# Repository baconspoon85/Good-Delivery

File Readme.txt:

Good Delivery is a pair of 10x4u PCBs featuring:
-Standard stagger layout
	Proto built and tested. Fully functional.
-Alpha stagger layout
	Proto pending.
-RP2040 MCU
-Hotswap MX support (w/ option to solder the corner switches for better o-ring stability with 3-pin switches)
-Solder Alps support
-Physical compatibility with Acai by CBKBD
	-Centered USB
	-Gummy O-ring mount

Vial firmware supporting both the standard row stagger and alpha stagger is complete, courtesy of Flamwenco! Big thank you. Check his Cutiepie repo, also forked on my page.

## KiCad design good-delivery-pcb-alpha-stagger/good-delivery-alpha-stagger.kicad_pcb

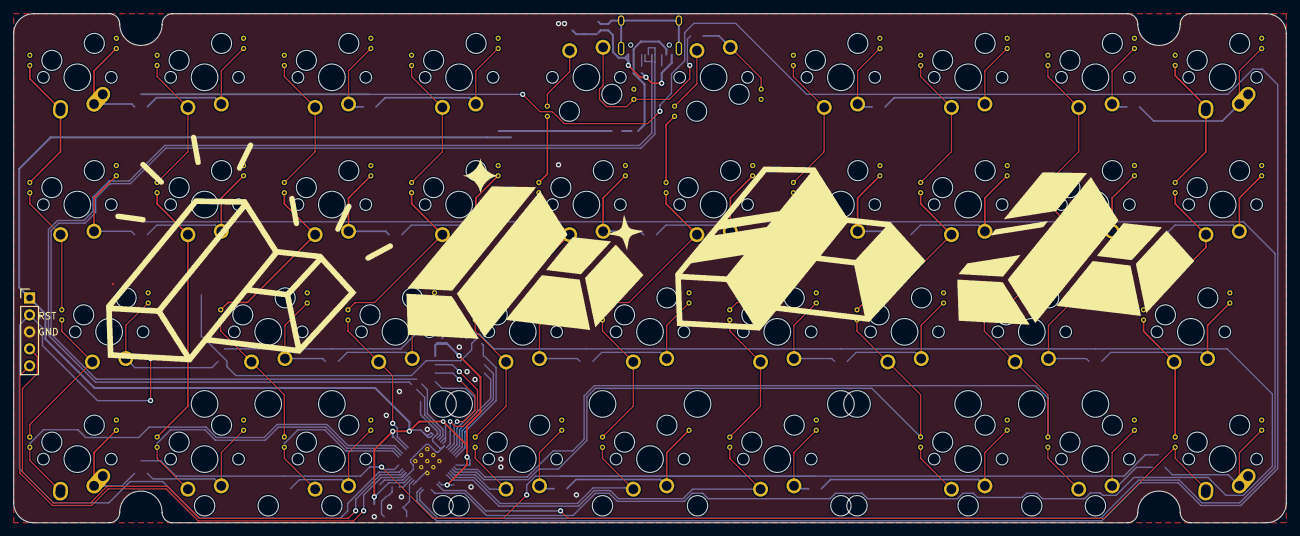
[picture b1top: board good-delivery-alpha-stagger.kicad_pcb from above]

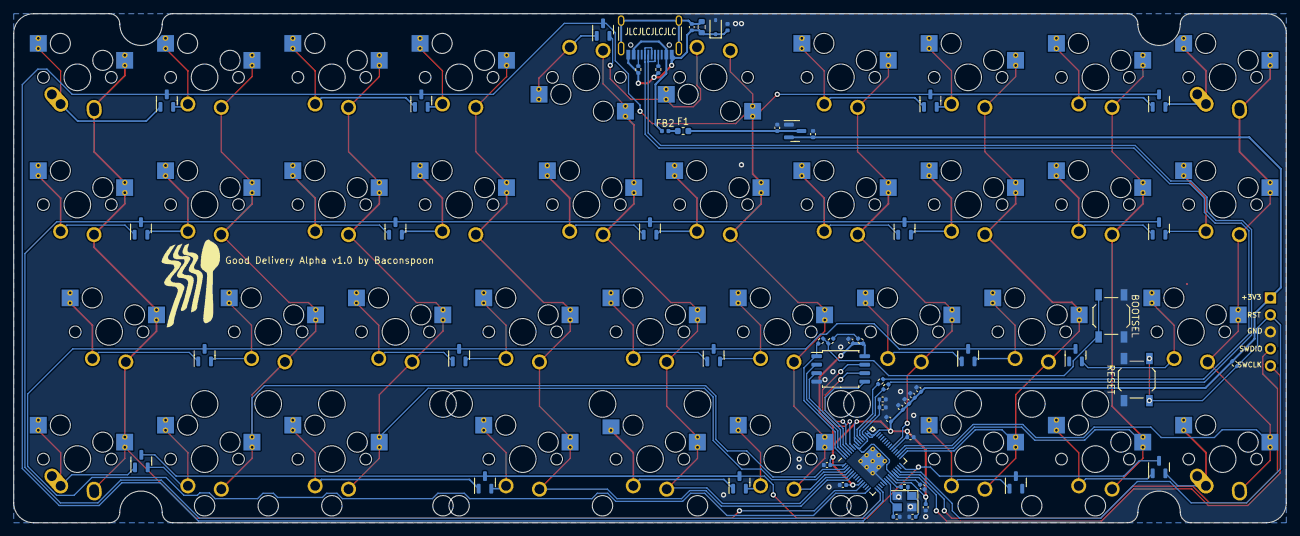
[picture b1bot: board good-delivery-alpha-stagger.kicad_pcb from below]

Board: 2 copper layers, 190.5 x 76.2 mm, 100 parts (60 on the bottom side), 80 nets.

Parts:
C1: 100nF; C_0402_1005Metric
C_1V-Decoup1, C_3V-Decoup2: 1u; C_0402_1005Metric
C_1V-Decoup2, C_1V-Decoup3, C_3V-Decoup3, C_3V-Decoup4, C_3V-Decoup5, C_3V-Decoup6, C_3V-Decoup7, C_3V-Decoup8, C_3V-Decoup9: 100n; C_0402_1005Metric
C_3V-Decoup1: 10u; C_0402_1005Metric
C_Crystal1, C_Crystal2: 22p; C_0402_1005Metric
C_Flash1: 100n; C_0402_1005Metric
C_LD1, C_LD2: 1u; C_0402_1005Metric
D1, D2, D3, D4, D5, D6, D7, D8, D9, D10, D11, D12, D13, D14, D15, D16, D17, D18, D19, D20: BAV70; SOT-23
D21: BSD3C051V; D_SOD-323
F1: 0603L075SLYR; Fuse_0603_1608Metric
FB1, FB2: BLM15PX121SN1D; L_0402_1005Metric
G1: Logo_Open_Hardware_Small; good-delivery-bars-silkscreen
G2: Logo_Open_Hardware_Small; baconspoon-logo-15mm
J2: SWD; PinHeader_1x05_P2.54mm_Vertical
J3: USB_C_Receptacle_USB2.0; USB_C_Receptacle_HRO_TYPE-C-31-M-12
MX1, MX4, MX5, MX6, MX7, MX8, MX9, MX10, MX11, MX12, MX13, MX14, MX15, MX16, MX17, MX18, MX20, MX21, MX22, MX24, MX25, MX26, MX28, MX29, MX30, MX31, MX32, MX33, MX34, MX35, MX38: MX-NoLED; 1U-MX-Hotswap-Alps-Solder-PadSwapped
MX2, MX36: MX-NoLED; 1U-MX-Hotswap-Alps-Solder
MX3, MX37: MX-NoLED; 1.5U-MX-Hotswap-Alps-Solder
MX19, MX27: MX-NoLED; 2U-MX-Hotswap-Alps-Solder-PadSwapped-ReversedStabilizers
MX23: MX-NoLED; 4,6,7,8,10u-MX-Hotswap-Alps-Solder-PadSwapped-ReversedStabi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
R1: 1M; R_0603_1608Metric
R2, R3: 5k1; R_0402_1005Metric
R_Crystal1: 1k; R_0402_1005Metric
R_DATA1, R_DATA2: 27; R_0402_1005Metric
R_Flash1, R_Flash2: 5k1; R_0402_1005Metric
R_Flash3: 1k; R_0402_1005Metric
R_RST1: 5k1; R_0402_1005Metric
SW1: RESET; SW_SPST_TL3342
SW2: BOOTSEL; SW_SPST_TL3342
U1: RP2040; RP2040-QFN-56
U2: W25Q128JVS; SOIC-8_5.23x5.23mm_P1.27mm
U3: XC6206P332MR; SOT-23
Y1: 12MHz; Crystal_SMD_3225-4Pin_3.2x2.5mm

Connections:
+1V1: C_1V-Decoup1.1, C_1V-Decoup2.1, C_1V-Decoup3.1, U1.23 (DVDD), U1.45 (VREG_VOUT), U1.50 (DVDD)
+3V3: C_3V-Decoup1.1, C_3V-Decoup2.1, C_3V-Decoup3.1, C_3V-Decoup4.1, C_3V-Decoup5.1, C_3V-Decoup6.1, C_3V-Decoup7.1, C_3V-Decoup8.1, C_3V-Decoup9.1, C_Flash1.1, C_LD2.1, J2.1, R_Flash1.1, R_RST1.1, U1.1 (IOVDD), U1.10 (IOVDD), U1.22 (IOVDD), U1.33 (IOVDD), U1.42 (IOVDD), U1.43 (ADC_AVDD), U1.44 (VREG_IN), U1.48 (USB_VDD), U1.49 (IOVDD), U2.8 (VCC), U3.2 (VO)
+5V: C_LD1.1, F1.2, U3.3 (VI)
COL 0: MX1.1 (COL), MX2.1 (COL), MX3.1 (COL), MX4.1 (COL), U1.31 (GPIO20)
COL 1: MX6.1 (COL), MX7.1 (COL), MX8.1 (COL), U1.30 (GPIO19)
COL 2: MX9.1 (COL), MX10.1 (COL), MX11.1 (COL), MX12.1 (COL), U1.29 (GPIO18)
COL 3: MX13.1 (COL), MX14.1 (COL), MX15.1 (COL), U1.34 (GPIO22)
COL 4: MX16.1 (COL), MX17.1 (COL), MX18.1 (COL), MX19.1 (COL), U1.4 (GPIO2)
COL 5: MX20.1 (COL), MX21.1 (COL), MX22.1 (COL), MX23.1 (COL), U1.5 (GPIO3)
COL 6: MX24.1 (COL), MX25.1 (COL), MX26.1 (COL), MX27.1 (COL), U1.6 (GPIO4)
COL 7: MX28.1 (COL), MX29.1 (COL), MX30.1 (COL), MX31.1 (COL), U1.3 (GPIO1)
COL 8: MX5.1 (COL), MX32.1 (COL), MX33.1 (COL), MX34.1 (COL), U1.2 (GPIO0)
COL 9: MX35.1 (COL), MX36.1 (COL), MX37.1 (COL), MX38.1 (COL), U1.11 (GPIO8)
CS: R_Flash3.2, U1.56 (QSPI_SS), U2.1 (~CS)
D+: J3.A6 (D+), J3.B6 (D+), R_DATA1.1
D-: J3.A7 (D-), J3.B7 (D-), R_DATA2.1
Earth: C1.1, J3.S1 (SHIELD), R1.1
GND: C_1V-Decoup1.2, C_1V-Decoup2.2, C_1V-Decoup3.2, C_3V-Decoup1.2, C_3V-Decoup2.2, C_3V-Decoup3.2, C_3V-Decoup4.2, C_3V-Decoup5.2, C_3V-Decoup6.2, C_3V-Decoup7.2, C_3V-Decoup8.2, C_3V-Decoup9.2, C_Crystal1.1, C_Crystal2.1, C_Flash1.2, C_LD1.2, C_LD2.2, D21.2 (A2), FB1.2, J2.3, SW1.1, SW2.1, U1.19 (TESTEN), U1.57 (GND), U2.4 (GND), U3.1 (GND), Y1.2, Y1.4
GNDPWR: C1.2, D21.1 (A1), FB1.1, J3.A1 (GND), J3.A12 (GND), J3.B1 (GND), J3.B12 (GND), R1.2, R2.2, R3.2
unnamed: C_Crystal2.2, R_Crystal1.1, Y1.1
unnamed: F1.1, FB2.2
unnamed: J3.A5 (CC1), R2.1
unnamed: J3.B5 (CC2), R3.1
unnamed: D1.2 (A), MX1.2 (ROW)
unnamed: D2.2 (A), MX2.2 (ROW)
unnamed: D3.2 (A), MX3.2 (ROW)
unnamed: D4.2 (A), MX4.2 (ROW)
unnamed: D18.2 (A), MX5.2 (ROW)
unnamed: D1.1 (A), MX6.2 (ROW)
unnamed: D2.1 (A), MX7.2 (ROW)
unnamed: D4.1 (A), MX8.2 (ROW)
unnamed: D5.2 (A), MX9.2 (ROW)
unnamed: D6.2 (A), MX10.2 (ROW)
unnamed: D7.2 (A), MX11.2 (ROW)
unnamed: D8.1 (A), MX12.2 (ROW)
unnamed: D5.1 (A), MX13.2 (ROW)
unnamed: D6.1 (A), MX14.2 (ROW)
unnamed: D7.1 (A), MX15.2 (ROW)
unnamed: D9.2 (A), MX16.2 (ROW)
unnamed: D10.2 (A), MX17.2 (ROW)
unnamed: D11.2 (A), MX18.2 (ROW)
unnamed: D12.2 (A), MX19.2 (ROW)
unnamed: D9.1 (A), MX20.2 (ROW)
unnamed: D10.1 (A), MX21.2 (ROW)
unnamed: D11.1 (A), MX22.2 (ROW)
unnamed: D12.1 (A), MX23.2 (ROW)
unnamed: D13.2 (A), MX24.2 (ROW)
unnamed: D14.2 (A), MX25.2 (ROW)
unnamed: D15.2 (A), MX26.2 (ROW)
unnamed: D16.2 (A), MX27.2 (ROW)
unnamed: D13.1 (A), MX28.2 (ROW)
unnamed: D14.1 (A), MX29.2 (ROW)
unnamed: D15.1 (A), MX30.2 (ROW)
unnamed: D16.1 (A), MX31.2 (ROW)
unnamed: D17.2 (A), MX32.2 (ROW)
unnamed: D19.2 (A), MX33.2 (ROW)
unnamed: D20.2 (A), MX34.2 (ROW)
unnamed: D17.1 (A), MX35.2 (ROW)
unnamed: D18.1 (A), MX36.2 (ROW)
unnamed: D19.1 (A), MX37.2 (ROW)
unnamed: D20.1 (A), MX38.2 (ROW)
unnamed: R_Flash1.2, R_Flash2.1
unnamed: R_Flash2.2, R_Flash3.1, SW2.2
unnamed: R_DATA2.2, U1.46 (USB_DM)
unnamed: R_DATA1.2, U1.47 (USB_DP)
QSPI_CLK: U1.52 (QSPI_SCLK), U2.6 (CLK)
RESET: J2.2, R_RST1.2, SW1.2, U1.26 (RUN)
ROW 0: D1.3 (K), D5.3 (K), D9.3 (K), D13.3 (K), D17.3 (K), U1.16 (GPIO13)
ROW 1: D2.3 (K), D6.3 (K), D10.3 (K), D14.3 (K), D18.3 (K), U1.15 (GPIO12)
ROW 2: D3.3 (K), D7.3 (K), D11.3 (K), D15.3 (K), D19.3 (K), U1.14 (GPIO11)
ROW 3: D4.3 (K), D8.3 (K), D12.3 (K), D16.3 (K), D20.3 (K), U1.28 (GPIO17)
SD0: U1.53 (QSPI_SD0), U2.5 (DI(IO0))
SD1: U1.55 (QSPI_SD1), U2.2 (DO(IO1))
SD2: U1.54 (QSPI_SD2), U2.3 (IO2)
SD3: U1.51 (QSPI_SD3), U2.7 (IO3)
SWCLK: J2.5, U1.24 (SWCLK)
SWDIO: J2.4, U1.25 (SWD)
VBUS: FB2.1, J3.A4 (VBUS), J3.A9 (VBUS), J3.B4 (VBUS), J3.B9 (VBUS)
XTAL_IN: C_Crystal1.2, U1.20 (XIN), Y1.3
XTAL_OUT: R_Crystal1.2, U1.21 (XOUT)

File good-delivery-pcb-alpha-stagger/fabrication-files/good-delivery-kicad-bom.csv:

Comment,Designator,Footprint,JLCPCB Part#
1uF,C_1V-Decoup1,C_0402_1005Metric,C52923
100nF,C_1V-Decoup2,C_0402_1005Metric,C2655418
100nF,C_1V-Decoup3,C_0402_1005Metric,C2655418
10uF,C_3V-Decoup1,C_0402_1005Metric,C15525
1uF,C_3V-Decoup2,C_0402_1005Metric,C52923
100nF,C_3V-Decoup3,C_0402_1005Metric,C2655418
100nF,C_3V-Decoup4,C_0402_1005Metric,C2655418
100nF,C_3V-Decoup5,C_0402_1005Metric,C2655418
100nF,C_3V-Decoup6,C_0402_1005Metric,C2655418
100nF,C_3V-Decoup7,C_0402_1005Metric,C2655418
100nF,C_3V-Decoup8,C_0402_1005Metric,C2655418
100nF,C_3V-Decoup9,C_0402_1005Metric,C2655418
22pF,C_Crystal1,C_0402_1005Metric,C1555
22pF,C_Crystal2,C_0402_1005Metric,C1555
100nF,C_Flash1,C_0402_1005Metric,C2655418
1uF,C_LD1,C_0402_1005Metric,C52923
1uF,C_LD2,C_0402_1005Metric,C52923
100nF,C1,C_0402_1005Metric,C2655418
BAV70,D1,SOT-23,C154830
BAV70,D10,SOT-23,C154830
BAV70,D11,SOT-23,C154830
BAV70,D12,SOT-23,C154830
BAV70,D13,SOT-23,C154830
BAV70,D14,SOT-23,C154830
BAV70,D15,SOT-23,C154830
BAV70,D16,SOT-23,C154830
BAV70,D17,SOT-23,C154830
BAV70,D18,SOT-23,C154830
BAV70,D19,SOT-23,C154830
BAV70,D2,SOT-23,C154830
BAV70,D20,SOT-23,C154830
BSD3C051V,D21,D_SOD-323,C151996
BAV70,D3,SOT-23,C154830
BAV70,D4,SOT-23,C154830
BAV70,D5,SOT-23,C154830
BAV70,D6,SOT-23,C154830
BAV70,D7,SOT-23,C154830
BAV70,D8,SOT-23,C154830
BAV70,D9,SOT-23,C154830
0603L075SLYR,F1,Fuse_0603_1608Metric,C207016
BLM15PX121SN1D,FB1,L_0402_1005Metric,C88970
BLM15PX121SN1D,FB2,L_0402_1005Metric,C88970
USB_C_Receptacle_USB2.0,J3,USB_C_Receptacle_HRO_TYPE-C-31-M-12,C165948
1k ohm,R_Crystal1,R_0402_1005Metric,C279987
27 ohm,R_DATA1,R_0402_1005Metric,C25100
27 ohm,R_DATA2,R_0402_1005Metric,C25100
5.1k ohm,R_Flash1,R_0402_1005Metric,C103086
5.1k ohm,R_Flash2,R_0402_1005Metric,C103086
1k ohm,R_Flash3,R_0402_1005Metric,C279987
5.1k ohm,R_RST1,R_0402_1005Metric,C103086
1M ohm,R1,R_0603_1608Metric,C3016422
5.1k ohm,R2,R_0402_1005Metric,C103086
5.1k ohm,R3,R_0402_1005Metric,C103086
RESET,SW1,SW_SPST_TL3342,C318884
BOOTSEL,SW2,SW_SPST_TL3342,C318884
RP2040,U1,RP2040-QFN-56,C2040
W25Q128JVS,U2,SOIC-8_5.23x5.23mm_P1.27mm,C2613930
XC6206P332MR,U3,SOT-23,C5446
12MHz,Y1,Crystal_SMD_3225-4Pin_3.2x2.5mm,C9002

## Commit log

2023-10-22 Added option to solder MX corner switches for improved gummy o-ring support with 3-pin switches.
2023-10-23 Add alpha stagger PCB
2023-10-24 Update Readme.txt
    Update to PCB features and development status.
2023-10-24 Add proto pcb images and kle image
2023-10-24 Add images to readme
2023-10-25 Update Readme.txt
    Announce completed vial firmware.
2023-10-25 Vial Firmware Upload
    Vial firmware UF2, courtesy of Flamwenco.
2023-10-26 Update Readme.txt
    minor correction: columnar stagger to row stagger
2023-10-29 add dual stagger plate outline and fr4 gerbers
